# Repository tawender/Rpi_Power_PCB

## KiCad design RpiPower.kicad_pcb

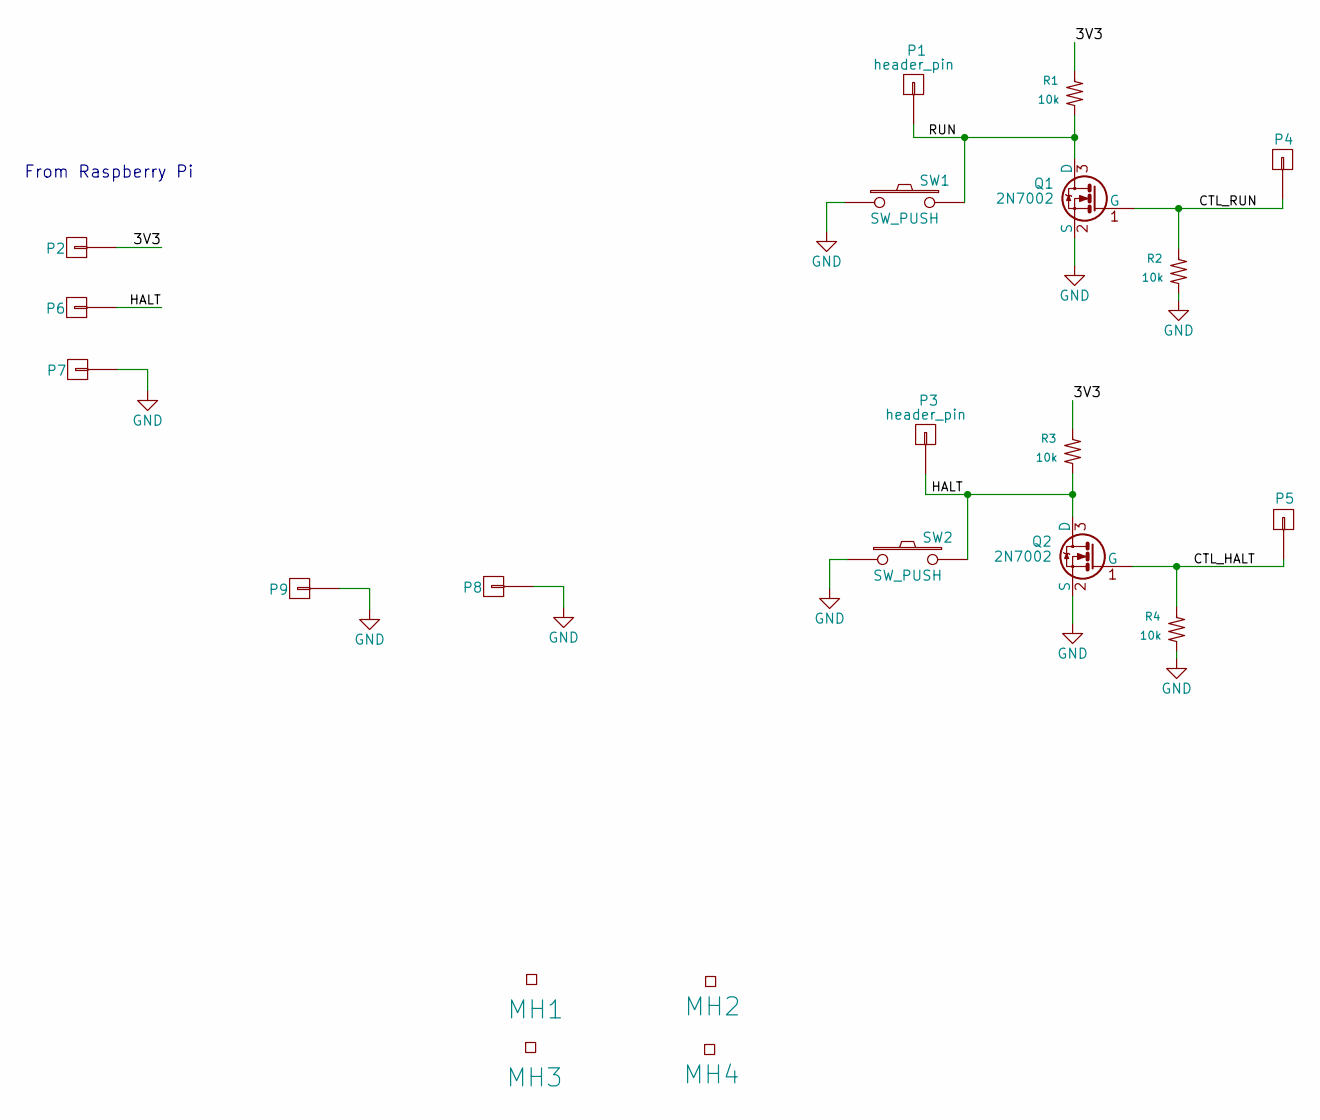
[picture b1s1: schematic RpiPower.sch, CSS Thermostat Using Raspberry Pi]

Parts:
MH1, MH2, MH3, MH4: mount_hole; Rpi_mt_hole
P1, P2, P3, P4, P5, P6, P7, P8, P9: header_pin; Hdr_Pin
Q1, Q2: 2N7002; SOT23; manufacturer pn 2N7002-7-F
R1, R2, R3, R4: 10k; 0805; manufacturer pn RC0603FR-07200RL
SW1, SW2: SW_PUSH; SW_tact_SPST_RA_thru; manufacturer pn TL6110DF300QP

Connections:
/3V3: P2.1, R1.2, R3.2
/CTL_HALT: P5.1, Q2.1 (G), R4.2
/CTL_RUN: P4.1, Q1.1 (G), R2.2
/HALT: P3.1, P6.1, Q2.3 (D), R3.1, SW2.2
/RUN: P1.1, Q1.3 (D), R1.1, SW1.2
GND: P7.1, P8.1, P9.1, Q1.2 (S), Q2.2 (S), R2.1, R4.1, SW1.1, SW2.1

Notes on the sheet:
From Raspberry Pi

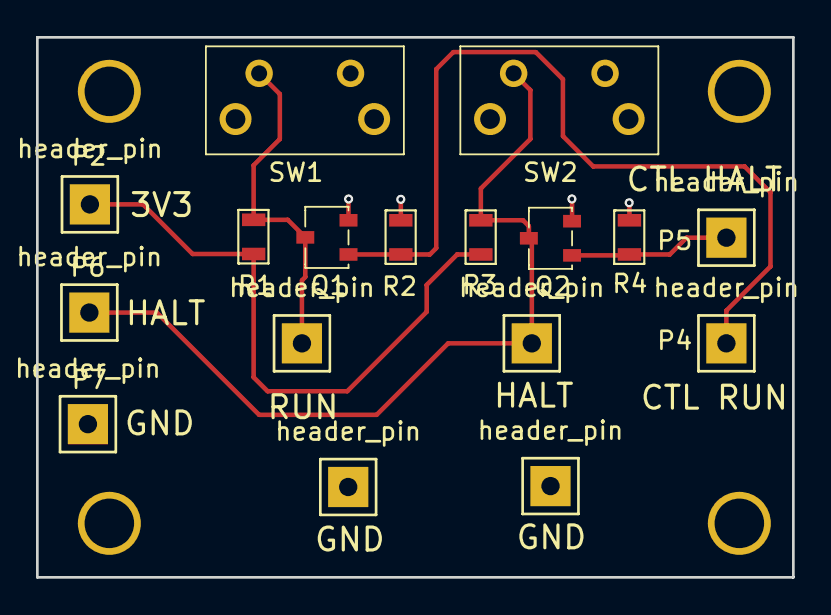
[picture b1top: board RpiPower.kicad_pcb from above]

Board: 2 copper layers, 42.0 x 30.0 mm, 21 parts (0 on the bottom side), 6 nets.

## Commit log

2017-08-01 changed from Raspberry pi 40-pin header to single pin headers to make the pcb smaller (cut size in half so half the cost)
2017-08-02 added pdf of schematic
2017-08-15 added notes document
